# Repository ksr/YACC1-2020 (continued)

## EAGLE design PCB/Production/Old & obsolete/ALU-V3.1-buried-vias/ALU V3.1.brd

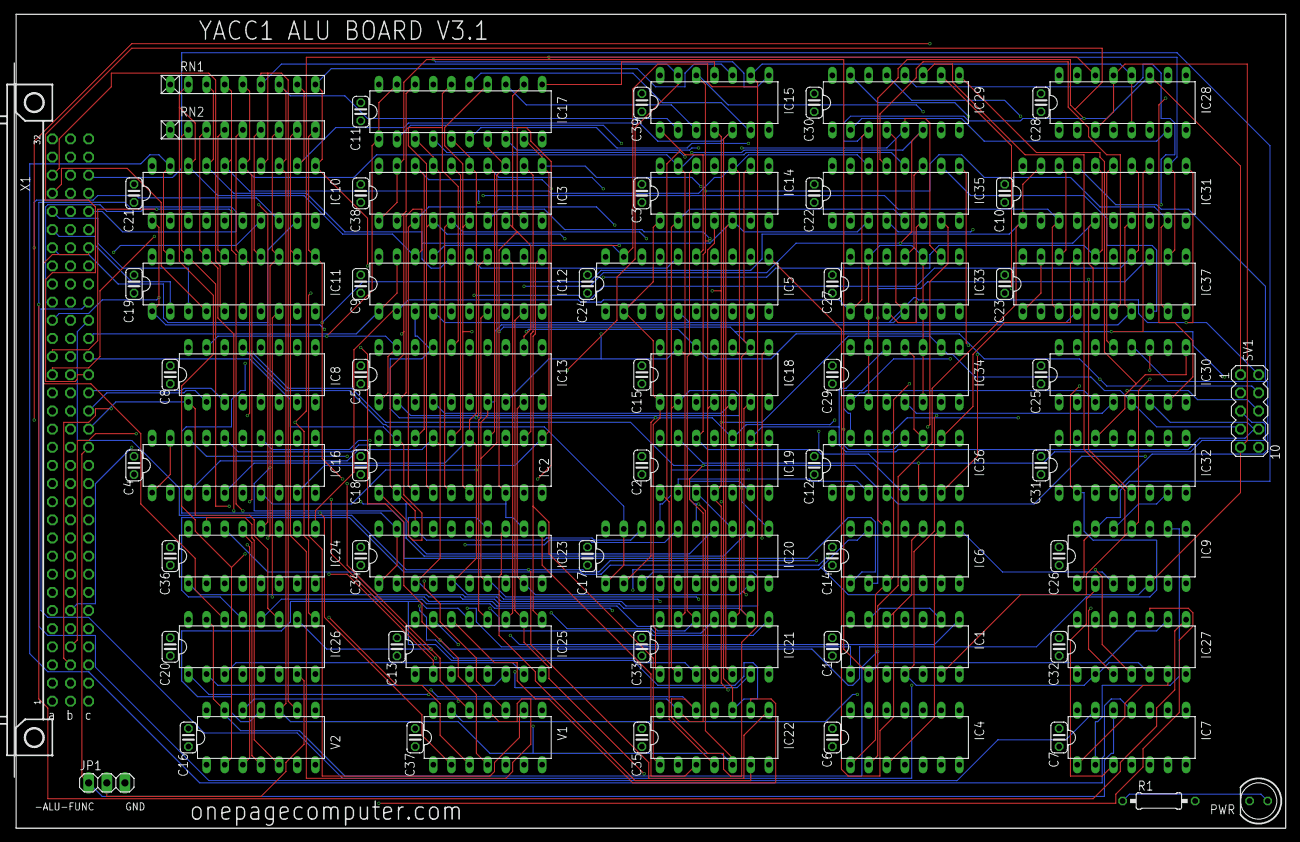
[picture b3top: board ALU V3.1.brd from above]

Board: 4 copper layers, 177.8 x 114.0 mm, 85 parts (0 on the bottom side), 159 nets.

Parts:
C1, C2, C3, C4, C5, C6, C7, C8, C9, C10, C11, C12, C13, C14, C15, C16, C17, C18, C19, C20, C22, C23, C24, C25, C26, C27, C28, C29, C30, C31, C32, C33, C34, C35, C36, C37, C38, C39: .1uf; C025-024X044
C21: ,1uf; C025-024X044
IC1: 74ALS04N; DIL14
IC2: 74LS240N; DIL20
IC3, IC12, IC13, IC16, IC17, IC20, IC23, IC31, IC37: 74LS244N; DIL20
IC4: 74LS00N; DIL14
IC5: 74LS374N; DIL20
IC6: 74ALS08N; DIL14
IC7, IC21, IC22: 74LS32N; DIL14
IC8: 74LS138N; DIL16
IC9: 74LS74N; DIL14
IC10, IC11: 74LS245N; DIL20
IC14, IC15, IC27, IC33, IC34: 74LS86N; DIL14
IC18, IC19: 74LS08N; DIL14
IC24, IC25: 74LS85N; DIL16
IC26: 74LS251N; DIL16
IC28, IC32: 74LS153N; DIL16
IC29, IC30: 74LS194N; DIL16
IC35, IC36: 74LS283N; DIL16
JP1: 1X03
PWR: LED5MM
R1: 330; 0207/10
RN1, RN2: 10k; RN-9
SV1: MA05-2
V1, V2: 744078N; DIL14
X1: FABC96R

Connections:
-AC-LD: IC1.9, IC1.13, X1.C22
-AC-LD-INV: IC1.1, IC2.1, IC2.19, X1.C20
-AC-RD: IC12.1, IC12.19, X1.C21
-ADD: IC6.1, IC8.7
-ADD/SUB: IC4.1, IC6.3, IC37.1, IC37.19
-ALU-FUNC: IC7.12, JP1.1, X1.C15
-ALU-IO-EN: IC7.11, IC10.19, IC11.19
-AND: IC8.13, IC20.1, IC20.19
-BUS-EN: IC7.13, X1.C28
-BUS-OUT: IC1.8, IC10.1, IC11.1
-DATA: IC8.15, IC13.1, IC13.19
-OR: IC8.12, IC23.1, IC23.19
-RESET: IC9.1, IC9.13, X1.C30
-SHIFT: IC4.2, IC8.10, IC31.1, IC31.19
-SR-LD: IC1.5, X1.C23
-SUB: IC1.3, IC6.2, IC8.14
-XOR: IC8.11, IC17.1, IC17.19
-ZERO: IC8.9, IC16.1, IC16.19
AC-LD: IC1.12, IC5.11, IC6.10
AC-LD-INV: IC1.2, IC3.1, IC3.19, IC27.9
ACI-DATA0: IC2.18, IC3.18, IC5.3
ACI-DATA1: IC2.16, IC3.16, IC5.4
ACI-DATA2: IC2.14, IC3.14, IC5.7
ACI-DATA3: IC2.12, IC3.12, IC5.8
ACI-DATA4: IC2.9, IC3.9, IC5.13
ACI-DATA5: IC2.7, IC3.7, IC5.14
ACI-DATA6: IC2.5, IC3.5, IC5.17
ACI-DATA7: IC2.3, IC3.3, IC5.18
ACO-DATA0: IC5.2, IC12.2, IC14.1, IC18.1, IC21.1, IC24.9, IC28.11, IC29.3, IC33.1, SV1.1
ACO-DATA1: IC5.5, IC12.4, IC14.4, IC18.4, IC21.4, IC24.11, IC29.4, IC33.4, SV1.2
ACO-DATA2: IC5.6, IC12.6, IC14.9, IC18.9, IC21.9, IC24.14, IC29.5, IC33.9, SV1.3
ACO-DATA3: IC5.9, IC12.8, IC14.12, IC18.12, IC21.12, IC24.1, IC29.6, IC30.2, IC33.12, SV1.4
ACO-DATA4: IC5.12, IC12.11, IC15.12, IC19.12, IC22.1, IC25.9, IC29.7, IC30.3, IC34.1, SV1.5
ACO-DATA5: IC5.15, IC12.13, IC15.1, IC19.1, IC22.4, IC25.11, IC30.4, IC34.4, SV1.6
ACO-DATA6: IC5.16, IC12.15, IC15.4, IC19.4, IC22.9, IC25.14, IC30.5, IC34.9, SV1.7
ACO-DATA7: IC5.19, IC12.17, IC15.9, IC19.9, IC22.12, IC25.1, IC28.5, IC28.12, IC30.6, IC34.12, SV1.8
ALU0: IC8.1, IC26.11, IC29.9, IC30.9, IC32.14, X1.C16
ALU1: IC8.2, IC26.10, IC29.10, IC30.10, IC32.2, X1.C17
ALU2: IC8.3, IC26.9, IC28.14, X1.C18
ALU3: IC6.12, IC28.2, X1.C19
BDATA0: IC10.18, IC12.18, IC13.2, IC14.2, IC18.2, IC21.2, IC24.10, IC35.5, RN1.2, V2.2
BDATA1: IC10.17, IC12.16, IC13.4, IC14.5, IC18.5, IC21.5, IC24.12, IC35.3, RN1.3, V2.3
BDATA2: IC10.16, IC12.14, IC13.6, IC14.10, IC18.10, IC21.10, IC24.13, IC35.14, RN1.4, V2.4
BDATA3: IC10.15, IC12.12, IC13.8, IC14.13, IC18.13, IC21.13, IC24.15, IC35.12, RN1.5, V2.5
BDATA4: IC10.14, IC12.9, IC13.11, IC15.13, IC19.13, IC22.2, IC25.10, IC36.5, RN1.6, V2.9
BDATA5: IC10.13, IC12.7, IC13.13, IC15.2, IC19.2, IC22.5, IC25.12, IC36.3, RN1.7, V2.10
BDATA6: IC10.12, IC12.5, IC13.15, IC15.5, IC19.5, IC22.10, IC25.13, IC36.14, RN1.8, V2.11
BDATA7: IC10.11, IC12.3, IC13.17, IC15.10, IC19.10, IC22.13, IC25.15, IC36.12, RN1.9, V2.12
BDATA8: IC11.18, RN2.2, V1.2
BDATA9: IC11.17, RN2.3, V1.3
BDATA10: IC11.16, RN2.4, V1.4
BDATA11: IC11.15, RN2.5, V1.5
BDATA12: IC11.14, RN2.6, V1.9
BDATA13: IC11.13, RN2.7, V1.10
BDATA14: IC11.12, RN2.8, V1.11
BDATA15: IC11.11, RN2.9, V1.12
BR-COND: IC27.8, X1.C24
C/SHIFT: IC6.13, IC9.5, IC26.12, IC28.3, IC28.13, SV1.9
CO/BO: IC7.1, IC27.6
DATA0: IC10.2, X1.A19
DATA1: IC10.3, X1.A20
DATA2: IC10.4, X1.A21
DATA3: IC10.5, X1.A22
DATA4: IC10.6, X1.A23
DATA5: IC10.7, X1.A24
DATA6: IC10.8, X1.A25
DATA7: IC10.9, X1.A26
DATA8: IC11.2, X1.A27
DATA9: IC11.3, X1.A28
DATA10: IC11.4, X1.A29
DATA11: IC11.5, X1.A30
DATA12: IC11.6, X1.B3
DATA13: IC11.7, X1.B4
DATA14: IC11.8, X1.B5
DATA15: IC11.9, X1.B6
GND: C1.2, C2.2, C3.2, C4.2, C5.2, C6.2, C7.2, C8.2, C9.2, C10.2, C11.2, C12.2, C13.2, C14.2, C15.2, C16.2, C17.2, C18.2, C19.2, C20.2, C21.2, C22.2, C23.2, C24.2, C25.2, C26.2, C27.2, C28.2, C29.2, C30.2, C31.2, C32.2, C33.2, C34.2, C35.2, C36.2, C37.2, C38.2, C39.2, IC1.7, IC1.11, IC2.10, IC3.10, IC4.4, IC4.5, IC4.7, IC4.9, IC4.10, IC4.12, IC4.13, IC5.1, IC5.10, IC6.7, IC7.4, IC7.5, IC7.7, IC7.9, IC7.10, IC8.4, IC8.5, IC8.8, IC9.7, IC10.10, IC11.10, IC12.10, IC13.10, IC14.7, IC15.7, IC16.2, IC16.4, IC16.6, IC16.8, IC16.10, IC16.11, IC16.13, IC16.15, IC16.17, IC17.10, IC18.7, IC19.7, IC20.10, IC21.7, IC22.7, IC23.10, IC24.2, IC24.4, IC24.8, IC25.8, IC26.8, IC27.7, IC27.12, IC27.13, IC28.1, IC28.4, IC28.6, IC28.8, IC28.10, IC28.15, IC29.8, IC30.8, IC31.10, IC32.1, IC32.3, IC32.6, IC32.8, IC32.10, IC32.11, IC32.12, IC32.13, IC32.15, IC33.7, IC34.7, IC35.8, IC36.8, IC37.10, JP1.3, PWR.K, SV1.10, V1.7, V2.7, X1.A1, X1.A32, X1.B1, X1.B32, X1.C1, X1.C32
IN: IC26.14, X1.C26
INV-IN0: IC2.2, IC3.2, IC13.18, IC16.18, IC17.18, IC20.18, IC23.18, IC31.18, IC37.18
INV-IN1: IC2.4, IC3.4, IC13.16, IC16.16, IC17.16, IC20.16, IC23.16, IC31.16, IC37.16
INV-IN2: IC2.6, IC3.6, IC13.14, IC16.14, IC17.14, IC20.14, IC23.14, IC31.14, IC37.14
INV-IN3: IC2.8, IC3.8, IC13.12, IC16.12, IC17.12, IC20.12, IC23.12, IC31.12, IC37.12
INV-IN4: IC2.11, IC3.11, IC13.9, IC16.9, IC17.9, IC20.9, IC23.9, IC31.9, IC37.9
INV-IN5: IC2.13, IC3.13, IC13.7, IC16.7, IC17.7, IC20.7, IC23.7, IC31.7, IC37.7
INV-IN6: IC2.15, IC3.15, IC13.5, IC16.5, IC17.5, IC20.5, IC23.5, IC31.5, IC37.5
INV-IN7: IC2.17, IC3.17, IC13.3, IC16.3, IC17.3, IC20.3, IC23.3, IC31.3, IC37.3
unnamed: IC27.4, IC36.9
unnamed: IC27.3, IC35.7
unnamed: IC4.3, IC6.9
unnamed: IC26.7, JP1.2
unnamed: IC6.8, IC9.3
unnamed: IC6.4, IC26.15, V2.13
unnamed: IC7.3, IC9.2
unnamed: IC6.11, IC27.1
unnamed: IC9.12, IC32.7
unnamed: IC33.6, IC35.2
unnamed: IC34.6, IC36.2
unnamed: PWR.A, R1.1
unnamed: IC33.8, IC35.15
unnamed: IC33.11, IC35.11
unnamed: IC33.3, IC35.6
unnamed: IC34.3, IC36.6
unnamed: IC34.8, IC36.15
unnamed: IC34.11, IC36.11
unnamed: IC35.4, IC37.2
unnamed: IC35.1, IC37.4
unnamed: IC35.13, IC37.6
unnamed: IC35.10, IC37.8
unnamed: IC36.4, IC37.11
unnamed: IC36.1, IC37.13
unnamed: IC36.13, IC37.15
unnamed: IC36.10, IC37.17
unnamed: IC35.9, IC36.7
unnamed: IC24.5, IC25.4
unnamed: IC24.6, IC25.3
unnamed: IC24.7, IC25.2
unnamed: IC25.7, IC26.3
unnamed: IC25.6, IC26.2
unnamed: IC25.5, IC26.1
unnamed: IC6.5, V1.13
unnamed: IC6.6, IC26.13
unnamed: IC26.5, IC27.10
unnamed: IC29.15, IC31.2, IC32.5
unnamed: IC29.14, IC31.4
unnamed: IC29.13, IC31.6
unnamed: IC29.12, IC31.8
unnamed: IC30.15, IC31.11
unnamed: IC30.14, IC31.13
unnamed: IC30.13, IC31.15
unnamed: IC30.12, IC31.17, IC32.4
unnamed: IC28.7, IC29.2
unnamed: IC28.9, IC30.7
unnamed: IC21.3, IC23.2
unnamed: IC21.6, IC23.4
unnamed: IC21.8, IC23.6
unnamed: IC21.11, IC23.8
unnamed: IC22.3, IC23.11
unnamed: IC22.6, IC23.13
unnamed: IC22.8, IC23.15
unnamed: IC22.11, IC23.17
unnamed: IC18.3, IC20.2
unnamed: IC18.6, IC20.4
unnamed: IC18.8, IC20.6
unnamed: IC18.11, IC20.8
unnamed: IC19.11, IC20.11
unnamed: IC19.3, IC20.13
unnamed: IC19.6, IC20.15
unnamed: IC19.8, IC20.17
unnamed: IC14.3, IC17.2
unnamed: IC14.6, IC17.4
unnamed: IC14.8, IC17.6
unnamed: IC14.11, IC17.8
unnamed: IC15.11, IC17.11
unnamed: IC15.3, IC17.13
unnamed: IC15.6, IC17.15
unnamed: IC15.8, IC17.17
SHIFT-OUT: IC7.2, IC9.9
SR-LD: IC1.6, IC9.11, IC29.11, IC30.11
SUB: IC1.4, IC27.2, IC27.5, IC33.2, IC33.5, IC33.10, IC33.13, IC34.2, IC34.5, IC34.10, IC34.13
VCC: C1.1, C2.1, C3.1, C4.1, C5.1, C6.1, C7.1, C8.1, C9.1, C10.1, C11.1, C12.1, C13.1, C14.1, C15.1, C16.1, C17.1, C18.1, C19.1, C20.1, C21.1, C22.1, C23.1, C24.1, C25.1, C26.1, C27.1, C28.1, C29.1, C30.1, C31.1, C32.1, C33.1, C34.1, C35.1, C36.1, C37.1, C38.1, C39.1, IC1.14, IC2.20, IC3.20, IC4.14, IC5.20, IC6.14, IC7.14, IC8.6, IC8.16, IC9.4, IC9.10, IC9.14, IC10.20, IC11.20, IC12.20, IC13.20, IC14.14, IC15.14, IC16.20, IC17.20, IC18.14, IC19.14, IC20.20, IC21.14, IC22.14, IC23.20, IC24.3, IC24.16, IC25.16, IC26.4, IC26.16, IC27.14, IC28.16, IC29.1, IC29.16, IC30.1, IC30.16, IC31.20, IC32.16, IC33.14, IC34.14, IC35.16, IC36.16, IC37.20, R1.2, RN1.1, RN2.1, V1.14, V2.14, X1.A2, X1.A31, X1.B2, X1.B31, X1.C2, X1.C31

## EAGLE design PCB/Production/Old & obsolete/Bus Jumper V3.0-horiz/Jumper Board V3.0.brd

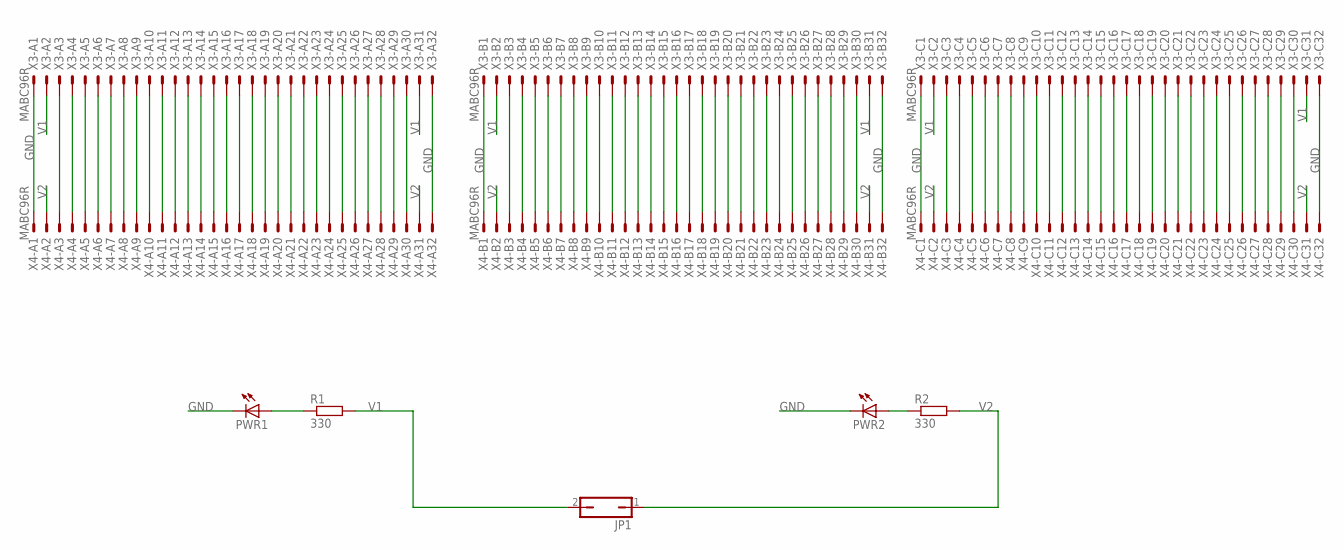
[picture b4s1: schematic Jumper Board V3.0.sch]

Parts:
JP1: JP1Q; JP1
PWR1, PWR2: LED5MM
R1, R2: 330; 0207/10
X3, X4: MABC96R

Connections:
GND: PWR1.K (C), PWR2.K (C), X3.A1, X3.A32, X3.B1, X3.B32, X3.C1, X3.C32, X4.A1, X4.A32, X4.B1, X4.B32, X4.C1, X4.C32
unnamed: X3.A3, X4.A3
unnamed: X3.A4, X4.A4
unnamed: X3.A5, X4.A5
unnamed: X3.A6, X4.A6
unnamed: X3.A7, X4.A7
unnamed: X3.A8, X4.A8
unnamed: X3.A9, X4.A9
unnamed: X3.A10, X4.A10
unnamed: X3.A11, X4.A11
unnamed: X3.A12, X4.A12
unnamed: X3.A13, X4.A13
unnamed: X3.A14, X4.A14
unnamed: X3.A15, X4.A15
unnamed: X3.A16, X4.A16
unnamed: X3.A17, X4.A17
unnamed: X3.A18, X4.A18
unnamed: X3.A19, X4.A19
unnamed: X3.A20, X4.A20
unnamed: X3.A21, X4.A21
unnamed: X3.A22, X4.A22
unnamed: X3.A23, X4.A23
unnamed: X3.A24, X4.A24
unnamed: X3.A25, X4.A25
unnamed: X3.A26, X4.A26
unnamed: X3.A27, X4.A27
unnamed: X3.A28, X4.A28
unnamed: X3.A29, X4.A29
unnamed: X3.A30, X4.A30
unnamed: PWR1.A, R1.1
unnamed: PWR2.A, R2.1
unnamed: X3.B3, X4.B3
unnamed: X3.B4, X4.B4
unnamed: X3.B5, X4.B5
unnamed: X3.B6, X4.B6
unnamed: X3.B7, X4.B7
unnamed: X3.B8, X4.B8
unnamed: X3.B9, X4.B9
unnamed: X3.B10, X4.B10
unnamed: X3.B11, X4.B11
unnamed: X3.B12, X4.B12
unnamed: X3.B13, X4.B13
unnamed: X3.B14, X4.B14
unnamed: X3.B15, X4.B15
unnamed: X3.B16, X4.B16
unnamed: X3.B17, X4.B17
unnamed: X3.B18, X4.B18
unnamed: X3.B19, X4.B19
unnamed: X3.B20, X4.B20
unnamed: X3.B21, X4.B21
unnamed: X3.B22, X4.B22
unnamed: X3.B23, X4.B23
unnamed: X3.B24, X4.B24
unnamed: X3.B25, X4.B25
unnamed: X3.B26, X4.B26
unnamed: X3.B27, X4.B27
unnamed: X3.B28, X4.B28
unnamed: X3.B29, X4.B29
unnamed: X3.B30, X4.B30
unnamed: X3.C3, X4.C3
unnamed: X3.C4, X4.C4
unnamed: X3.C5, X4.C5
unnamed: X3.C6, X4.C6
unnamed: X3.C7, X4.C7
unnamed: X3.C8, X4.C8
unnamed: X3.C9, X4.C9
unnamed: X3.C10, X4.C10
unnamed: X3.C11, X4.C11
unnamed: X3.C12, X4.C12
unnamed: X3.C13, X4.C13
unnamed: X3.C14, X4.C14
unnamed: X3.C15, X4.C15
unnamed: X3.C16, X4.C16
unnamed: X3.C17, X4.C17
unnamed: X3.C18, X4.C18
unnamed: X3.C19, X4.C19
unnamed: X3.C20, X4.C20
unnamed: X3.C21, X4.C21
unnamed: X3.C22, X4.C22
unnamed: X3.C23, X4.C23
unnamed: X3.C24, X4.C24
unnamed: X3.C25, X4.C25
unnamed: X3.C26, X4.C26
unnamed: X3.C27, X4.C27
unnamed: X3.C28, X4.C28
unnamed: X3.C29, X4.C29
unnamed: X3.C30, X4.C30
V1: JP1.2, R1.2, X3.A2, X3.A31, X3.B2, X3.B31, X3.C2, X3.C31
V2: JP1.1, R2.2, X4.A2, X4.A31, X4.B2, X4.B31, X4.C2, X4.C31

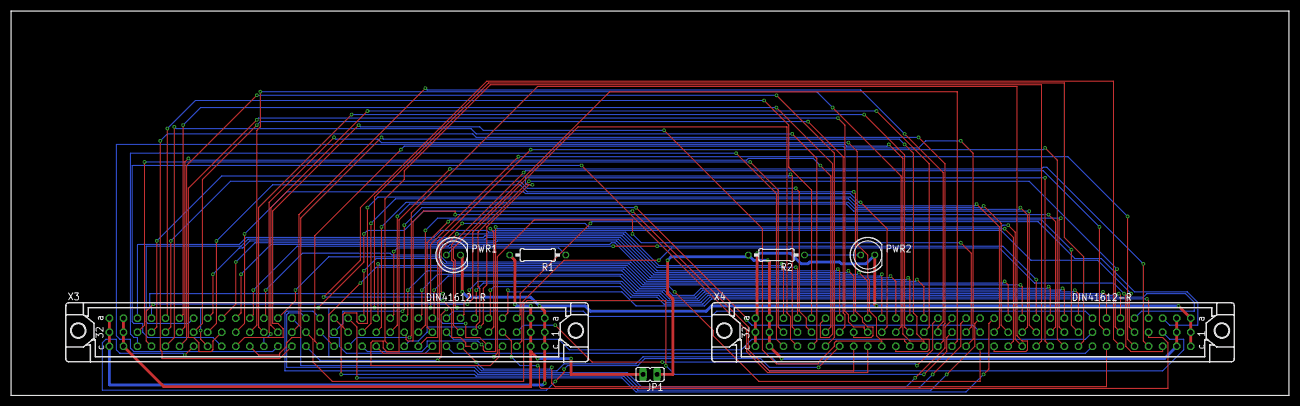
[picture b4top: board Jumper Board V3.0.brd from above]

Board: 2 copper layers, 231.1 x 69.5 mm, 7 parts (0 on the bottom side), 89 nets.

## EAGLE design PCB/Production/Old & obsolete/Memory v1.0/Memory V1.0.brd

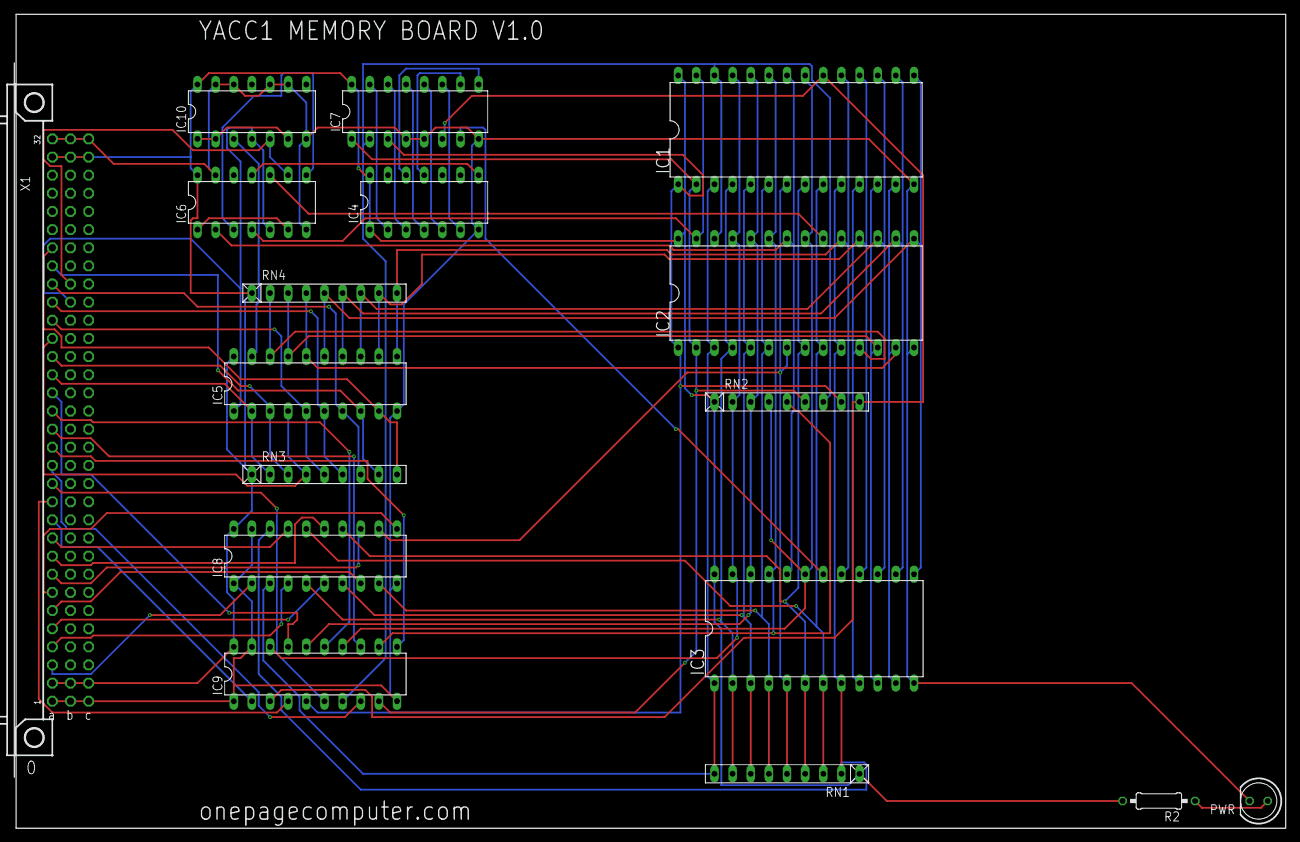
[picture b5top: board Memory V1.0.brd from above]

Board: 2 copper layers, 177.8 x 114.0 mm, 17 parts (0 on the bottom side), 69 nets.

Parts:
IC1, IC2: DIL28-6
IC3: DIL24
IC4: 74ALS30N; DIL14
IC5: 74LS245N; DIL20
IC6: 74LS04N; DIL14
IC7: 74LS138N; DIL16
IC8, IC9: 74LS244N; DIL20
IC10: 74ALS00N; DIL14
PWR: LED5MM
R2: 330; 0207/10
RN1, RN2, RN3, RN4: RN-9
X1: FABC96R

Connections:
-HI-RAM: IC2.20, IC6.10
-MEM-RD: IC5.1, IC6.5, IC10.4, X1.B23
-MEM-WR: IC6.9, IC10.5, X1.B24
-ROM: IC3.18, IC7.7
ADDR0: IC8.2, X1.A3
ADDR1: IC8.4, X1.A4
ADDR2: IC8.6, X1.A5
ADDR3: IC8.8, X1.A6
ADDR4: IC8.11, X1.A7
ADDR5: IC8.13, X1.A8
ADDR6: IC8.15, X1.A9
ADDR7: IC8.17, X1.A10
ADDR8: IC9.2, X1.A11
ADDR9: IC9.4, X1.A12
ADDR10: IC9.6, X1.A13
ADDR11: IC9.8, X1.A14
ADDR12: IC9.11, X1.A15
ADDR13: IC9.13, X1.A16
ADDR14: IC9.15, X1.A17
ADDR15: IC9.17, X1.A18
BADDR0: IC1.10, IC2.10, IC3.8, IC8.18, RN1.2
BADDR1: IC1.9, IC2.9, IC3.7, IC8.16, RN1.3
BADDR2: IC1.8, IC2.8, IC3.6, IC8.14, RN1.4
BADDR3: IC1.7, IC2.7, IC3.5, IC8.12, RN1.5
BADDR4: IC1.6, IC2.6, IC3.4, IC8.9, RN1.6
BADDR5: IC1.5, IC2.5, IC3.3, IC8.7, RN1.7
BADDR6: IC1.4, IC2.4, IC3.2, IC8.5, RN1.8
BADDR7: IC1.3, IC2.3, IC3.1, IC8.3, RN1.9
BADDR8: IC1.25, IC2.25, IC3.23, IC9.18, RN2.2
BADDR9: IC1.24, IC2.24, IC3.22, IC9.16, RN2.3
BADDR10: IC1.21, IC2.21, IC3.19, IC9.14, RN2.4
BADDR11: IC1.23, IC2.23, IC3.21, IC9.12, RN2.5
BADDR12: IC1.2, IC2.2, IC7.1, IC9.9, RN2.6
BADDR13: IC1.26, IC2.26, IC7.2, IC9.7, RN2.7
BADDR14: IC1.1, IC2.1, IC7.3, IC9.5, RN2.8
BADDR15: IC1.20, IC7.6, IC9.3, RN2.9
BDATA0: IC1.11, IC2.11, IC3.9, IC5.18, RN4.2
BDATA1: IC1.12, IC2.12, IC3.10, IC5.17, RN4.3
BDATA2: IC1.13, IC2.13, IC3.11, IC5.16, RN4.4
BDATA3: IC1.15, IC2.15, IC3.13, IC5.15, RN4.5
BDATA4: IC1.16, IC2.16, IC3.14, IC5.14, RN4.6
BDATA5: IC1.17, IC2.17, IC3.15, IC5.13, RN4.7
BDATA6: IC1.18, IC2.18, IC3.16, IC5.12, RN4.8
BDATA7: IC1.19, IC2.19, IC3.17, IC5.11, RN4.9
DATA0: IC5.2, RN3.2, X1.A19
DATA1: IC5.3, RN3.3, X1.A20
DATA2: IC5.4, RN3.4, X1.A21
DATA3: IC5.5, RN3.5, X1.A22
DATA4: IC5.6, RN3.6, X1.A23
DATA5: IC5.7, RN3.7, X1.A24
DATA6: IC5.8, RN3.8, X1.A25
DATA7: IC5.9, RN3.9, X1.A26
GND: IC1.14, IC2.14, IC3.12, IC4.7, IC5.10, IC6.7, IC6.13, IC7.4, IC7.5, IC7.8, IC8.1, IC8.10, IC8.19, IC9.1, IC9.10, IC9.19, IC10.7, IC10.9, IC10.10, IC10.12, IC10.13, PWR.K, X1.A1, X1.A32, X1.B1, X1.B32, X1.C1, X1.C32
MEM-RD: IC6.1, IC6.6
unnamed: IC4.12, IC7.9
unnamed: IC6.3, IC6.8
unnamed: IC1.22, IC2.22, IC3.20, IC6.2
unnamed: IC1.27, IC2.27, IC6.4
unnamed: IC4.11, IC7.10
unnamed: IC4.6, IC7.11
unnamed: IC4.5, IC7.12
unnamed: IC4.4, IC7.13
unnamed: IC4.3, IC7.14
unnamed: IC4.2, IC7.15
unnamed: PWR.A, R2.1
unnamed: IC10.1, IC10.2, IC10.6
unnamed: IC5.19, IC10.3
unnamed: IC4.8, IC6.11
VCC: IC1.28, IC2.28, IC3.24, IC4.1, IC4.14, IC5.20, IC6.14, IC7.16, IC8.20, IC9.20, IC10.14, R2.2, RN1.1, RN2.1, RN3.1, RN4.1, X1.A2, X1.A31, X1.B2, X1.B31, X1.C2, X1.C31

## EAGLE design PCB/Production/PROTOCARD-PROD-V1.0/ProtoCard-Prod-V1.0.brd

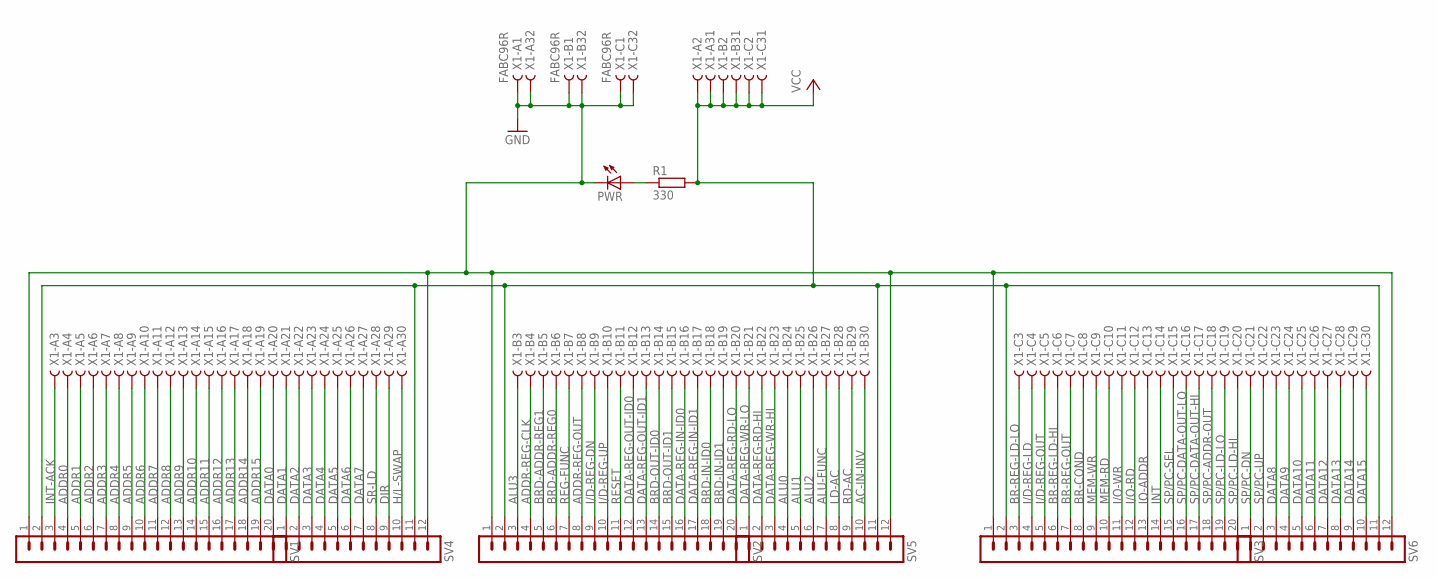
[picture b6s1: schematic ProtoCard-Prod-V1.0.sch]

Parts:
PWR: LED5MM
R1: 330; 0207/10
SV1, SV2, SV3: MA20-1
SV4, SV5, SV6: MA12-1
X1: FABC96R

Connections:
AC-IN-INV: SV5.10, X1.B30
ADDR0: SV1.4, X1.A4
ADDR1: SV1.5, X1.A5
ADDR2: SV1.6, X1.A6
ADDR3: SV1.7, X1.A7
ADDR4: SV1.8, X1.A8
ADDR5: SV1.9, X1.A9
ADDR6: SV1.10, X1.A10
ADDR7: SV1.11, X1.A11
ADDR8: SV1.12, X1.A12
ADDR9: SV1.13, X1.A13
ADDR10: SV1.14, X1.A14
ADDR11: SV1.15, X1.A15
ADDR12: SV1.16, X1.A16
ADDR13: SV1.17, X1.A17
ADDR14: SV1.18, X1.A18
ADDR15: SV1.19, X1.A19
ADDR-REG-CLK: SV2.4, X1.B4
ADDR-REG-OUT: SV2.8, X1.B8
ALU0: SV5.4, X1.B24
ALU1: SV5.5, X1.B25
ALU2: SV5.6, X1.B26
ALU3: SV2.3, X1.B3
ALU-FUNC: SV5.7, X1.B27
BR-COND: SV3.8, X1.C8
BR-REG-LD-HI: SV3.6, X1.C6
BR-REG-LD-LO: SV3.3, X1.C3
BR-REG-OUT: SV3.7, X1.C7
BRD-ADDR-REG0: SV2.6, X1.B6
BRD-ADDR-REG1: SV2.5, X1.B5
BRD-IN-ID0: SV2.18, X1.B18
BRD-IN-ID1: SV2.19, X1.B19
BRD-OUT-ID0: SV2.14, X1.B14
BRD-OUT-ID1: SV2.15, X1.B15
DATA0: SV1.20, X1.A20
DATA1: SV4.1, X1.A21
DATA2: SV4.2, X1.A22
DATA3: SV4.3, X1.A23
DATA4: SV4.4, X1.A24
DATA5: SV4.5, X1.A25
DATA6: SV4.6, X1.A26
DATA7: SV4.7, X1.A27
DATA8: SV6.3, X1.C23
DATA9: SV6.4, X1.C24
DATA10: SV6.5, X1.C25
DATA11: SV6.6, X1.C26
DATA12: SV6.7, X1.C27
DATA13: SV6.8, X1.C28
DATA14: SV6.9, X1.C29
DATA15: SV6.10, X1.C30
DATA-REG-IN-ID0: SV2.16, X1.B16
DATA-REG-IN-ID1: SV2.17, X1.B17
DATA-REG-OUT-ID0: SV2.12, X1.B12
DATA-REG-OUT-ID1: SV2.13, X1.B13
DATA-REG-RD-HI: SV5.2, X1.B22
DATA-REG-RD-LO: SV2.20, X1.B20
DATA-REG-WR-HI: SV5.3, X1.B23
DATA-REG-WR-LO: SV5.1, X1.B21
DIR: SV4.9, X1.A29
GND: PWR.K (C), SV1.1, SV2.1, SV3.1, SV4.12, SV5.12, SV6.12, X1.A1, X1.A32, X1.B1, X1.B32, X1.C1, X1.C32
H/L-SWAP: SV4.10, X1.A30
I/D-REG-DN: SV2.9, X1.B9
I/D-REG-LD: SV3.4, X1.C4
I/D-REG-OUT: SV3.5, X1.C5
I/D-REG-UP: SV2.10, X1.B10
I/O-RD: SV3.12, X1.C12
I/O-WR: SV3.11, X1.C11
INT: SV3.14, X1.C14
INT-ACK: SV1.3, X1.A3
IO-ADDR: SV3.13, X1.C13
LD-AC: SV5.8, X1.B28
MEM-RD: SV3.10, X1.C10
MEM-WR: SV3.9, X1.C9
unnamed: PWR.A, R1.1
RD-AC: SV5.9, X1.B29
REG-FUNC: SV2.7, X1.B7
RESET: SV2.11, X1.B11
SP/PC-ADDR-OUT: SV3.18, X1.C18
SP/PC-DATA-OUT-HI: SV3.17, X1.C17
SP/PC-DATA-OUT-LO: SV3.16, X1.C16
SP/PC-DN: SV6.1, X1.C21
SP/PC-LD-HI: SV3.20, X1.C20
SP/PC-LD-LO: SV3.19, X1.C19
SP/PC-SEL: SV3.15, X1.C15
SP/PC-UP: SV6.2, X1.C22
SR-LD: SV4.8, X1.A28
VCC: R1.2, SV1.2, SV2.2, SV3.2, SV4.11, SV5.11, SV6.11, X1.A2, X1.A31, X1.B2, X1.B31, X1.C2, X1.C31

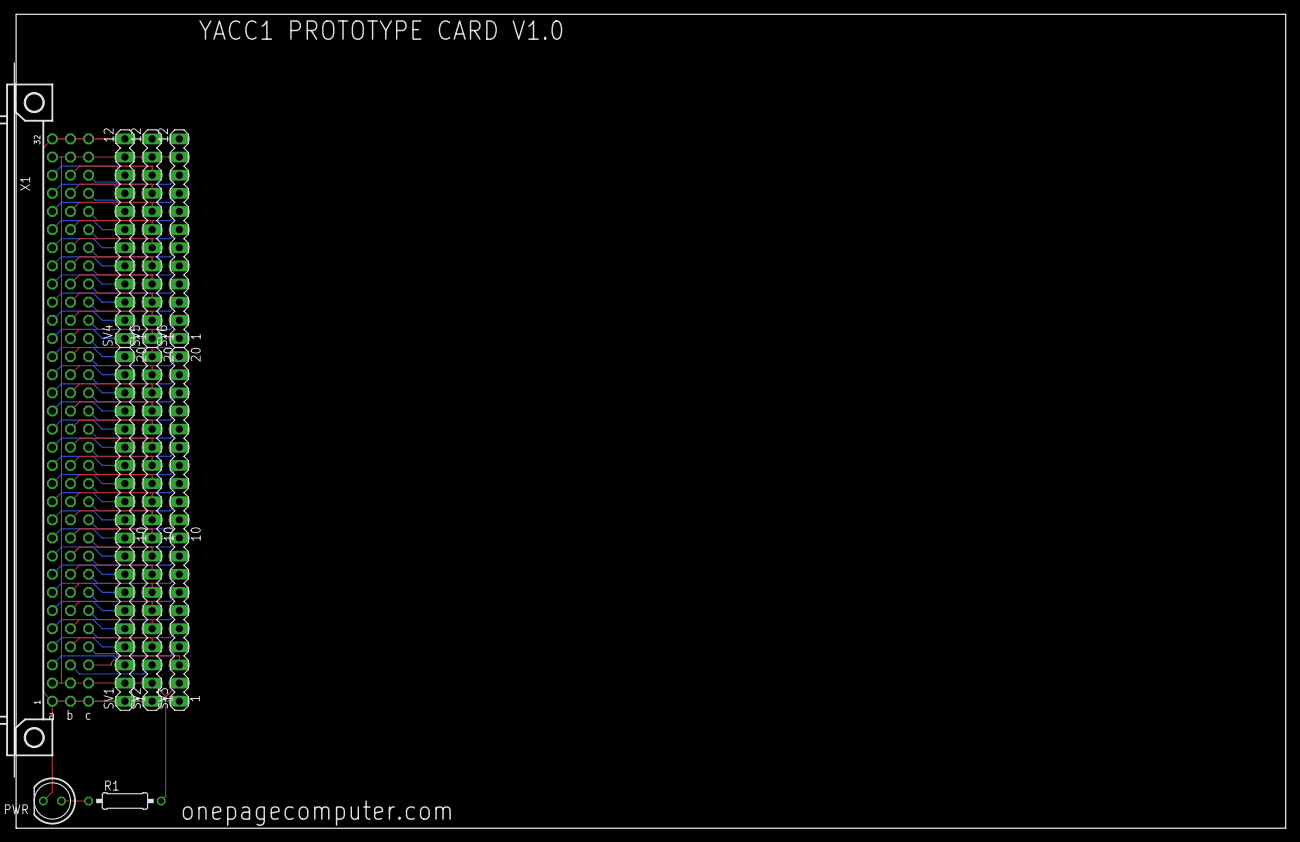
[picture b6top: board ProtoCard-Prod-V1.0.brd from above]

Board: 2 copper layers, 177.8 x 114.0 mm, 9 parts (0 on the bottom side), 87 nets.

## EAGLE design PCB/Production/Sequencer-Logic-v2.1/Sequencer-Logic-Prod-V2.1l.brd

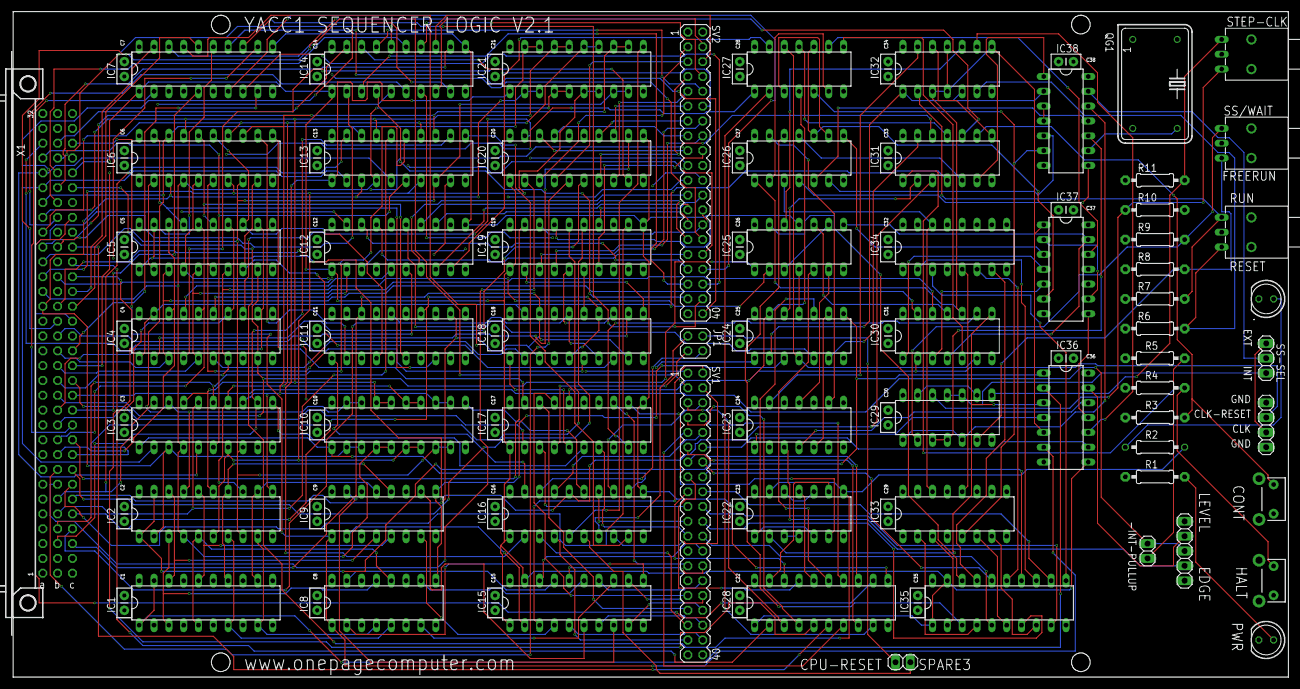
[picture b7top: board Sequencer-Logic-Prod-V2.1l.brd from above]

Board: 4 copper layers, 218.4 x 114.0 mm, 104 parts (0 on the bottom side), 282 nets.

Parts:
-INT-PULLUP: 1X02
.: OUT; LED5MM
C1, C2, C3, C4, C5, C6, C7, C8, C9, C10, C11, C12, C13, C14, C15, C16, C17, C18, C19, C20, C21, C22, C23, C24, C25, C26, C27, C28, C29, C30, C31, C32, C33, C34, C35, C36, C37, C38: .1; CAP-PTH-SMALLEZ
CONT: SWITCH-MOMENTARY-2SIDE_EZ; TACTILE-PTH-SIDEEZ
HALT: SWITCH-MOMENTARY-2SIDE_EZ; TACTILE-PTH-SIDEEZ
IC1, IC2, IC4, IC5, IC11, IC15, IC18, IC35: 74LS244N; DIL20
IC3, IC6, IC7, IC10, IC12, IC13, IC14, IC16, IC17, IC19, IC20, IC21, IC28: 74LS374N; DIL20
IC8, IC9: 74LS175N; DIL16
IC22, IC29, IC32: 74ALS02N; DIL14
IC23: 74LS74N; DIL14
IC24, IC27, IC38: 74LS08N; DIL14
IC25, IC26, IC30: 74LS32N; DIL14
IC31, IC36, IC37: 74LS04N; DIL14
IC33, IC34: 74LS192N; DIL16
JP1: 2X02
JP2: PINHD-1X2; 1X02
JP3: 1X05
JP4: PINHD-1X4; 1X04
PWR: LED5MM
QG1: DIL14S
R1, R3, R4, R5, R6, R7, R8, R9, R10, R11: 10k; 0207/10
R2: 330; 0207/10
RESET: 9070-1W
SS-SEL: 1X03
SS/WAIT: 9070-1W
STEP-CLK: 9070-1W
SV1, SV2: MA20-2
X1: FABC96R

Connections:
-2-BYTE-OPERAND-SEL: IC5.1, IC5.19, IC16.16, IC31.3
-AC-LD: IC28.5, X1.C22
-AC-LD-INV: IC7.19, X1.C20
-AC-RD: IC28.2, X1.C21
-ALU-FUNC: IC7.6, X1.C15
-BRANCH-RD: IC13.1, IC16.2, IC21.1
-BUS-EN: IC7.1, IC12.1, IC14.1, IC15.1, IC15.19, IC16.1, IC17.1, IC19.1, IC20.1, IC28.1, IC35.1, IC35.19, IC36.8, X1.C28
-DO-INT: IC1.1, IC1.19, IC36.2
-FP-HALT: HALT.2, IC31.1, R4.1
-HALT-CONT: CONT.2, IC31.9, R3.1
-HL-SWAP: IC28.12, X1.C25
-INT: -INT-PULLUP.2, JP3.3, X1.C13
-INT-JMP: IC3.1, IC10.1, IC16.12
-INTA: IC17.2, X1.C14
-IO-ADDR-LD: IC7.2, X1.C11
-IO-RD: IC14.6, X1.B25
-IO-WR: IC14.9, X1.B26
-MEM-CPU-RESET: JP1.2, JP2.1
-MEM-RD: IC14.2, X1.B23
-MEM-WR: IC14.5, X1.B24
-ONE-OPERAND-SEL: IC4.1, IC4.19, IC18.19, IC31.4
-REG-DN: IC12.16, X1.B21
-REG-FUNC-LD: IC20.5, X1.B8
-REG-FUNC-RD: IC20.2, X1.B7
-REG-LD-HI: IC31.12, X1.B20
-REG-LD-LO: IC31.10, X1.B18
-REG-RD-HI: IC12.12, X1.B19
-REG-RD-LO: IC12.6, X1.B17
-REG-UP: IC12.19, X1.B22
-RESET: IC8.1, IC9.1, IC36.6, X1.C30
-SR-LD: IC28.6, X1.C23
-TMP-REG-LD0: IC14.15, X1.B28
-TMP-REG-LD1: IC14.19, X1.B30
-TMP-REG-RD0: IC14.12, X1.B27
-TMP-REG-RD1: IC14.16, X1.B29
-VMA: IC7.5, X1.C12
ADDR-REG-ID0: IC11.18, IC18.9, IC18.18, X1.C3
ADDR-REG-ID1: IC11.16, IC18.7, IC18.16, X1.C4
ADDR-REG-ID2: IC11.14, IC18.5, IC18.14, X1.C5
ADDR-REG-ID3: IC11.12, IC18.3, IC18.12, X1.C6
ALU0: IC7.9, X1.C16
ALU1: IC7.12, X1.C17
ALU2: IC7.15, X1.C18
ALU3: IC7.16, X1.C19
BR-COND: IC27.1, X1.C24
BR-TEST: IC27.2, IC28.9
BRANCH-LD-HI: IC13.11, IC16.9
BRANCH-LD-LO: IC16.5, IC21.11
BUS-LATCH-CLK: IC7.11, IC12.11, IC14.11, IC16.11, IC17.11, IC19.11, IC20.11, IC25.11, IC28.11
CADDR0: IC35.16, SV1.14
CADDR1: IC35.14, SV1.16
CADDR2: IC35.12, SV1.18
CADDR3: IC35.9, SV1.20
CADDR4: IC35.7, SV1.22
CADDR5: IC35.5, SV1.24
CADDR6: IC15.18, SV1.26
CADDR7: IC15.16, SV1.28
CADDR8: IC15.14, SV1.30
CADDR9: IC15.12, SV1.32
CADDR10: IC15.9, SV1.34
CADDR11: IC15.7, SV1.36
CADDR12: IC15.5, SV1.38
CADDR13: IC15.3, SV1.2
CNT-CLK: IC25.13, IC35.18
COUNT-FAULT: IC26.12, IC35.3
COUNT-RESET: IC26.3, IC33.14, IC34.14
DATA0: IC2.2, IC3.3, IC6.3, IC10.2, IC10.3, IC13.3, IC21.2, IC21.3, X1.A19
DATA1: IC2.4, IC3.4, IC6.4, IC10.4, IC10.5, IC13.4, IC21.4, IC21.5, X1.A20
DATA2: IC2.6, IC3.7, IC6.7, IC10.6, IC10.7, IC13.7, IC21.6, IC21.7, X1.A21
DATA3: IC2.8, IC3.8, IC6.8, IC10.8, IC10.9, IC13.8, IC21.8, IC21.9, X1.A22
DATA4: IC2.11, IC3.13, IC6.13, IC10.12, IC10.13, IC13.13, IC21.12, IC21.13, X1.A23
DATA5: IC2.13, IC3.14, IC6.14, IC10.14, IC10.15, IC13.14, IC21.14, IC21.15, X1.A24
DATA6: IC2.15, IC3.17, IC6.17, IC10.16, IC10.17, IC13.17, IC21.16, IC21.17, X1.A25
DATA7: IC2.17, IC3.18, IC6.18, IC10.18, IC10.19, IC13.18, IC21.18, IC21.19, X1.A26
DATA8: IC3.2, IC13.2, X1.A27
DATA9: IC3.5, IC13.5, X1.A28
DATA10: IC3.6, IC13.6, X1.A29
DATA11: IC3.9, IC13.9, X1.A30
DATA12: IC3.12, IC13.12, X1.B3
DATA13: IC3.15, IC13.15, X1.B4
DATA14: IC3.16, IC13.16, X1.B5
DATA15: IC3.19, IC13.19, X1.B6
DEST-ADDR: IC11.1, IC16.19
DO-HALT: IC23.9, IC26.13
DO-INT: IC2.1, IC2.19, IC24.8, IC36.1
EXTERNAL-SINGLESTEP-CLK: JP4.2, SS-SEL.3
FP-CLKH: IC29.12, R10.1, STEP-CLK.3
FP-CLKL: IC29.8, R11.2, STEP-CLK.1
FP-EXECUTE: IC32.6, R6.1, RESET.3
FP-FREERUN: IC29.2, R9.2, SS/WAIT.1
FP-HALT: IC24.12, IC31.2
FP-HALT-CONT: IC31.8, IC32.12
FP-RESET: IC32.2, R7.2, RESET.1
FP-SINGLE-STEP-CLK: IC29.10, IC29.11, SS-SEL.1
FP-SS: IC29.6, R8.1, SS/WAIT.3
FREE-RUN: IC29.3, IC29.4, IC38.10
GND: ..K, C1.2, C2.2, C3.2, C4.2, C5.2, C6.2, C7.2, C8.2, C9.2, C10.2, C11.2, C12.2, C13.2, C14.2, C15.2, C16.2, C17.2, C18.2, C19.2, C20.2, C21.2, C22.2, C23.2, C24.2, C25.2, C26.2, C27.2, C28.2, C29.2, C30.2, C31.2, C32.2, C33.2, C34.2, C35.2, C36.2, C37.2, C38.2, CONT.1, HALT.1, IC1.10, IC2.10, IC3.10, IC4.10, IC5.10, IC6.1, IC6.10, IC7.10, IC8.8, IC9.8, IC10.10, IC11.10, IC11.11, IC11.13, IC11.15, IC11.17, IC11.19, IC12.10, IC13.10, IC14.10, IC15.10, IC16.10, IC17.10, IC18.10, IC19.10, IC20.10, IC21.10, IC22.7, IC23.7, IC24.7, IC25.7, IC26.7, IC27.7, IC28.10, IC29.7, IC30.7, IC31.7, IC32.7, IC33.1, IC33.8, IC33.9, IC33.10, IC33.15, IC34.1, IC34.8, IC34.9, IC34.10, IC34.15, IC35.10, IC36.7, IC37.7, IC37.11, IC38.7, JP3.1, JP3.5, JP4.1, JP4.4, PWR.K, QG1.7, R6.2, R7.1, R8.2, R9.1, R10.2, R11.1, SV1.39, SV1.40, X1.A1, X1.A32, X1.B1, X1.B32, X1.C1, X1.C32
HALT-CLR: IC23.13, IC32.13
HARD-RESET1: IC29.9, IC29.13
INT-EDGE: IC23.3, JP3.2
INT-EN: IC17.12, IC22.6
INT-LD-HI: IC3.11, IC17.6
INT-LD-LO: IC10.11, IC16.15
INT-LEVEL: IC36.13, JP3.4
INT-START: IC17.9, IC30.9
IO-ADDR0: IC19.12, X1.C7
IO-ADDR1: IC19.15, X1.C8
IO-ADDR2: IC19.16, X1.C9
IO-ADDR3: IC19.19, X1.C10
LADDR-REG-ID0: IC18.11, IC19.2
LADDR-REG-ID1: IC18.13, IC19.5
LADDR-REG-ID2: IC18.15, IC19.6
LADDR-REG-ID3: IC18.17, IC19.9
LD-INS-REG: IC17.15, IC24.1
LD-INS-REG1: IC8.9, IC9.9, IC24.3
LREG-LD-HI: IC12.15, IC24.5
LREG-LD-ID0: IC4.11, IC20.16
LREG-LD-ID1: IC4.13, IC20.19
LREG-LD-ID2: IC4.15, IC12.2
LREG-LD-ID3: IC4.17, IC12.5
LREG-LD-LO: IC12.9, IC27.13
LREG-RD-ID0: IC4.2, IC20.6
LREG-RD-ID1: IC4.4, IC20.9
LREG-RD-ID2: IC4.6, IC20.12
LREG-RD-ID3: IC4.8, IC20.15
unnamed: IC33.12, IC34.5
unnamed: IC9.2, IC15.2
unnamed: IC9.7, IC15.4
unnamed: IC27.5, IC33.5, IC38.6
unnamed: IC1.18, IC2.18, IC9.4
unnamed: IC1.16, IC2.16, IC9.5
unnamed: IC33.3, IC35.2
unnamed: IC33.2, IC35.4
unnamed: IC33.6, IC35.6
unnamed: IC9.10, IC15.6
unnamed: IC33.7, IC35.8
unnamed: IC34.3, IC35.11
unnamed: IC34.2, IC35.13
unnamed: IC34.6, IC35.15
unnamed: IC34.7, IC35.17
unnamed: IC31.6, IC38.1
unnamed: IC1.14, IC2.14, IC9.12
unnamed: IC1.12, IC2.12, IC9.13
unnamed: IC1.9, IC2.9, IC8.4
unnamed: IC1.7, IC2.7, IC8.5
unnamed: IC1.5, IC2.5, IC8.12
unnamed: IC1.3, IC2.3, IC8.13
unnamed: IC9.15, IC15.8
unnamed: IC22.1, IC22.5, IC24.10
unnamed: IC22.3, IC22.4
unnamed: IC26.11, IC31.5
unnamed: IC22.2, IC30.8, IC36.3
unnamed: IC23.5, IC24.9
unnamed: IC23.1, IC36.4
unnamed: PWR.A, R1.1
unnamed: IC38.3, IC38.4
unnamed: IC25.12, IC32.10
unnamed: IC23.11, IC25.6
unnamed: IC8.2, IC15.11
unnamed: IC8.7, IC15.13
unnamed: IC8.10, IC15.15
unnamed: IC8.15, IC15.17
unnamed: IC26.5, IC38.11
unnamed: IC26.4, IC38.8
unnamed: IC38.9, QG1.8
unnamed: IC23.4, IC36.12
unnamed: IC36.11, IC37.8
unnamed: IC37.2, IC37.9
unnamed: IC25.3, IC25.9
unnamed: IC32.9, IC36.10
unnamed: IC25.10, IC30.11
unnamed: IC22.10, IC22.12
unnamed: -INT-PULLUP.1, R5.2
unnamed: IC27.9, IC37.12
unnamed: IC27.8, IC30.5
unnamed: IC24.4, IC27.12, IC30.6
unnamed: IC24.11, IC25.4
unnamed: IC26.2, IC27.6
unnamed: IC25.8, IC30.4, IC37.13
unnamed: IC27.11, IC31.11
unnamed: IC24.6, IC31.13
unnamed: ..A, R2.1
unnamed: IC26.8, IC37.3
unnamed: IC5.17, IC6.19, IC11.8
unnamed: IC5.2, IC6.2, IC18.2
unnamed: IC5.4, IC6.5, IC18.4
unnamed: IC5.6, IC6.6, IC18.6
unnamed: IC5.8, IC6.9, IC18.8
unnamed: IC5.11, IC6.12, IC11.2
unnamed: IC30.3, IC37.5
unnamed: IC5.13, IC6.15, IC11.4
unnamed: IC5.15, IC6.16, IC11.6
unnamed: IC30.1, IC37.4
unnamed: IC26.10, IC27.10, IC37.6
unnamed: IC26.9, IC27.3
OPERAND-CLK: IC6.11, IC17.19
OUT: IC22.8, IC22.13, R2.2, X1.C27
OUT-OFF: IC22.11, IC28.16
OUT-ON: IC22.9, IC28.19
READY: IC36.9, SV1.12
REG-LD-ID0: IC4.9, IC5.9, IC25.1, X1.B13
REG-LD-ID1: IC4.7, IC5.7, IC25.2, X1.B14
REG-LD-ID2: IC4.5, IC5.5, IC30.12, X1.B15
REG-LD-ID3: IC4.3, IC5.3, IC30.13, X1.B16
REG-RD-ID0: IC4.18, IC5.18, X1.B9
REG-RD-ID1: IC4.16, IC5.16, X1.B10
REG-RD-ID2: IC4.14, IC5.14, X1.B11
REG-RD-ID3: IC4.12, IC5.12, X1.B12
RESET: IC26.1, IC30.10, IC32.3, IC32.4, IC32.8, IC32.11, IC36.5, IC37.1
RUN: IC24.2, IC32.1, IC32.5, IC38.2
SINGLE-STEP-CLK: IC38.13, SS-SEL.2
SINGLE-STEP/WAIT: IC29.1, IC29.5, IC38.12
SOFT-HALT: IC25.5, IC28.15
SPARE3: IC16.6, JP2.2
SRC-ADDR: IC17.5, IC18.1
U-2-BYTE-OPERAND-SEL: IC16.17, SV1.10
U-AC-LD: IC28.4, SV1.7
U-AC-LD-INV: IC7.18, SV1.3
U-AC-RD: IC28.3, SV1.5
U-ALU-FUNC: IC7.7, SV2.34
U-BRANCH-RD: IC16.3, SV1.35
U-HL-SWAP: IC28.13, SV1.13
U-INT-JMP: IC16.13, SV1.6
U-INTA: IC17.3, SV1.19
U-IO-ADDR-LD: IC7.3, SV2.30
U-IO-RD: IC14.7, SV2.39
U-IO-WR: IC14.8, SV2.4
U-MEM-RD: IC14.3, SV2.35
U-MEM-WR: IC14.4, SV2.37
U-REG-DN: IC12.17, SV2.31
U-REG-FUNC-LD: IC20.4, SV2.5
U-REG-FUNC-RD: IC20.3, SV2.3
U-REG-RD-HI: IC12.13, SV2.27
U-REG-RD-LO: IC12.7, SV2.23
U-REG-UP: IC12.18, SV2.33
U-SR-LD: IC28.7, SV1.9
U-TMP-REG-LD0: IC14.14, SV2.8
U-TMP-REG-LD1: IC14.18, SV2.12
U-TMP-REG-RD0: IC14.13, SV2.6
U-TMP-REG-RD1: IC14.17, SV2.10
U-VMA: IC7.4, SV2.32
UADDR-REG-ID0: IC19.3, SV2.14
UADDR-REG-ID1: IC19.4, SV2.16
UADDR-REG-ID2: IC19.7, SV2.18
UADDR-REG-ID3: IC19.8, SV2.20
UALU0: IC7.8, SV2.36
UALU1: IC7.13, SV2.38
UALU2: IC7.14, SV2.40
UALU3: IC7.17, SV1.1
UBR-TEST: IC28.8, SV1.11
UBRANCH-LD-HI: IC16.8, SV1.4
UBRANCH-LD-LO: IC16.4, SV1.37
UCODE-CLK: IC26.6, IC38.5
UCODE-COUNT-RESET: IC17.16, IC24.13, IC27.4, IC30.2, JP4.3
UDEST-ADDR: IC16.18, JP1.4
UINT-EN: IC17.13, SV1.27
UINT-LD-HI: IC17.7, SV1.23
UINT-LD-LO: IC16.14, SV1.21
UINT-START: IC17.8, SV1.25
UIO-ADDR0: IC19.13, SV2.22
UIO-ADDR1: IC19.14, SV2.24
UIO-ADDR2: IC19.17, SV2.26
UIO-ADDR3: IC19.18, SV2.28
ULD-INS-REG: IC17.14, SV1.29
UOPERAND-CLK: IC17.18, SV1.33
UOUT-OFF: IC28.17, SV1.15
UOUT-ON: IC28.18, SV1.17
UREG-LD-HI: IC12.14, SV2.29
UREG-LD-ID0: IC20.17, SV2.15
UREG-LD-ID1: IC20.18, SV2.17
UREG-LD-ID2: IC12.3, SV2.19
UREG-LD-ID3: IC12.4, SV2.21
UREG-LD-LO: IC12.8, SV2.25
UREG-RD-ID0: IC20.7, SV2.7
UREG-RD-ID1: IC20.8, SV2.9
UREG-RD-ID2: IC20.13, SV2.11
UREG-RD-ID3: IC20.14, SV2.13
USOFT-HALT: IC28.14, SV1.8
USPARE3: IC16.7, JP1.1
USRC-ADDR: IC17.4, JP1.3
UUCODE-COUNT-RESET: IC17.17, SV1.31
VCC: C1.1, C2.1, C3.1, C4.1, C5.1, C6.1, C7.1, C8.1, C9.1, C10.1, C11.1, C12.1, C13.1, C14.1, C15.1, C16.1, C17.1, C18.1, C19.1, C20.1, C21.1, C22.1, C23.1, C24.1, C25.1, C26.1, C27.1, C28.1, C29.1, C30.1, C31.1, C32.1, C33.1, C34.1, C35.1, C36.1, C37.1, C38.1, IC1.2, IC1.4, IC1.6, IC1.8, IC1.11, IC1.13, IC1.15, IC1.17, IC1.20, IC2.20, IC3.20, IC4.20, IC5.20, IC6.20, IC7.20, IC8.16, IC9.16, IC10.20, IC11.20, IC12.20, IC13.20, IC14.20, IC15.20, IC16.20, IC17.20, IC18.20, IC19.20, IC20.20, IC21.20, IC22.14, IC23.2, IC23.10, IC23.12, IC23.14, IC24.14, IC25.14, IC26.14, IC27.14, IC28.20, IC29.14, IC30.14, IC31.14, IC32.14, IC33.4, IC33.11, IC33.16, IC34.4, IC34.11, IC34.16, IC35.20, IC36.14, IC37.14, IC38.14, QG1.14, R1.2, R3.2, R4.2, R5.1, RESET.2, SS/WAIT.2, STEP-CLK.2, SV2.1, SV2.2, X1.A2, X1.A31, X1.B2, X1.B31, X1.C2, X1.C31
